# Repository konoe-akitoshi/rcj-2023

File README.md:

# rcj-2023

Program of RoboCup Junior 2023 Soccer Open.

## Member

| Name      | Role                  | Links                                                                                |
| :-------- | :-------------------- | :----------------------------------------------------------------------------------- |
| Akitoshi  | Team Leader, Hardware | [Twitter](https://twitter.com/konoe_akitoshi), [Homepage](https://akitoshi-lab.dev/) |
| ryota2357 | Software (main)       | [Twitter](https://twitter.com/95s7k84695a), [Homepage](https://ryota2357.com/)       |
| sepa38    | Software (vision)     | [Twitter](https://twitter.com/sepa381), [AtCoder](https://atcoder.jp/users/sepa_38)  |
| gae       | Schedule, Chores      | [Twitter](https://twitter.com/gae_uec)                                               |

## Project Layout

```
.
├── Gyro              Gyro senssor (BNO5055) program.
├── LICENSE           MIT License.
├── MainProgram
│   ├── Program       Main (RP2040) program.
│   ├── Test          Test programs for main RP2040.
├── Motor
│   ├── Program       MotorDriver (ATMega328P) program.
│   └── Test          Test programs for MotorDriver.
├── README.md
├── Terminal
│   ├── Program       Main LCD (Wio Terminal) program.
│   └── Tests         Test programs for Main LCD.
└── Vison-M1n
    ├── Calibration   Check and calculate camera calibration paramaters.
    ├── Program       Vison (M1n) protrams.
    └── Tests         Test programs for Vision.
```

## Wiki

Our wiki are available at [Here](https://github.com/konoe-akitoshi/rcj-2023/wiki)

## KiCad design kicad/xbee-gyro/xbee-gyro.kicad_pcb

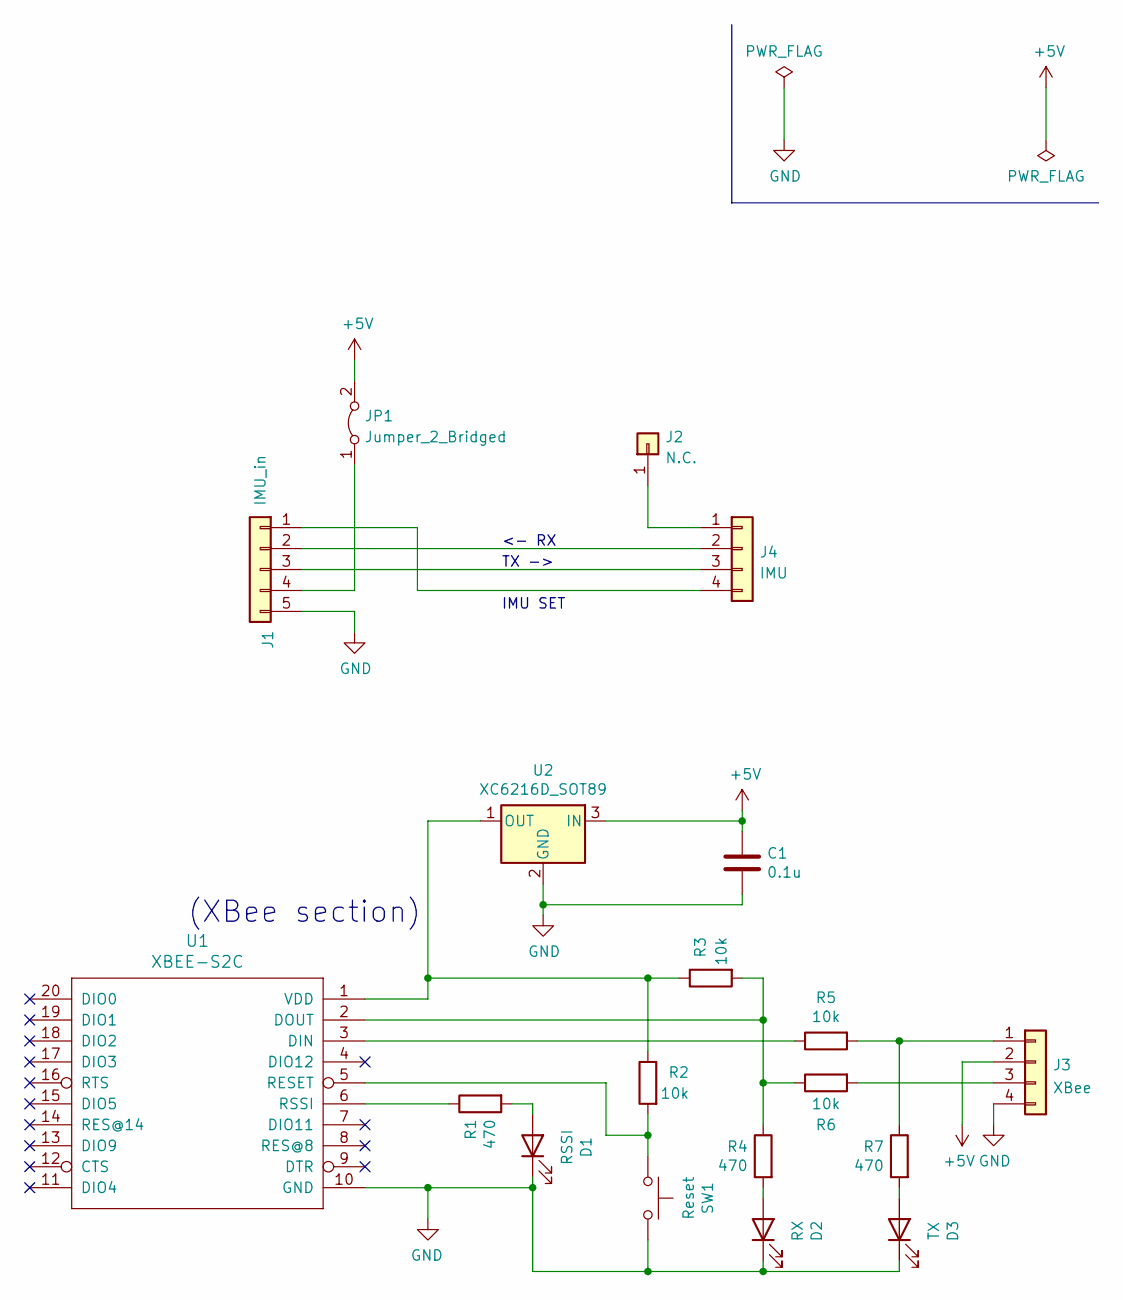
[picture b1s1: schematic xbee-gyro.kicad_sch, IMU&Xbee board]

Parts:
C1: 0.1u; C_0603_1608Metric_Pad1.08x0.95mm_HandSolder
D1: RSSI; LED_0603_1608Metric_Pad1.05x0.95mm_HandSolder
D2: RX; LED_0603_1608Metric_Pad1.05x0.95mm_HandSolder
D3: TX; LED_0603_1608Metric_Pad1.05x0.95mm_HandSolder
J1: IMU_in; PinHeader_1x05_P1.27mm_Vertical
J2: N.C.; PinHeader_1x01_P2.54mm_Vertical
J3: XBee; PinSocket_1x04_P2.54mm_Vertical
J4: IMU; PinSocket_1x04_P2.54mm_Vertical
JP1: Jumper_2_Bridged; SolderJumper-2_P1.3mm_Bridged_Pad1.0x1.5mm
R1, R4, R7: 470; R_0603_1608Metric_Pad0.98x0.95mm_HandSolder
R2, R3, R5, R6: 10k; R_0603_1608Metric_Pad0.98x0.95mm_HandSolder
SW1: Reset; THAU13-AB-R
U1: XBEE-S2C
U2: XC6216D_SOT89; SOT-89-3

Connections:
+5V: C1.1, J3.2, JP1.2 (B), U2.3 (IN)
GND: C1.2, D1.1 (K), D2.1 (K), D3.1 (K), J1.5, J3.4, SW1.2, U1.10 (GND), U2.2 (GND)
unnamed: D1.2 (A), R1.2
unnamed: D2.2 (A), R4.2
unnamed: D3.2 (A), R7.2
unnamed: J1.1, J4.4
unnamed: J1.2, J4.2
unnamed: J1.3, J4.3
unnamed: J1.4, JP1.1 (A)
unnamed: J2.1, J4.1
unnamed: J3.1, R5.2, R7.1
unnamed: J3.3, R6.2
unnamed: R1.1, U1.6 (RSSI)
unnamed: R2.1, R3.1, U1.1 (VDD), U2.1 (OUT)
unnamed: R2.2, SW1.1, U1.5 (RESET)
unnamed: R3.2, R4.1, R6.1, U1.2 (DOUT)
unnamed: R5.1, U1.3 (DIN)

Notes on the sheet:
<- RX
(XBee section)
TX ->
IMU SET

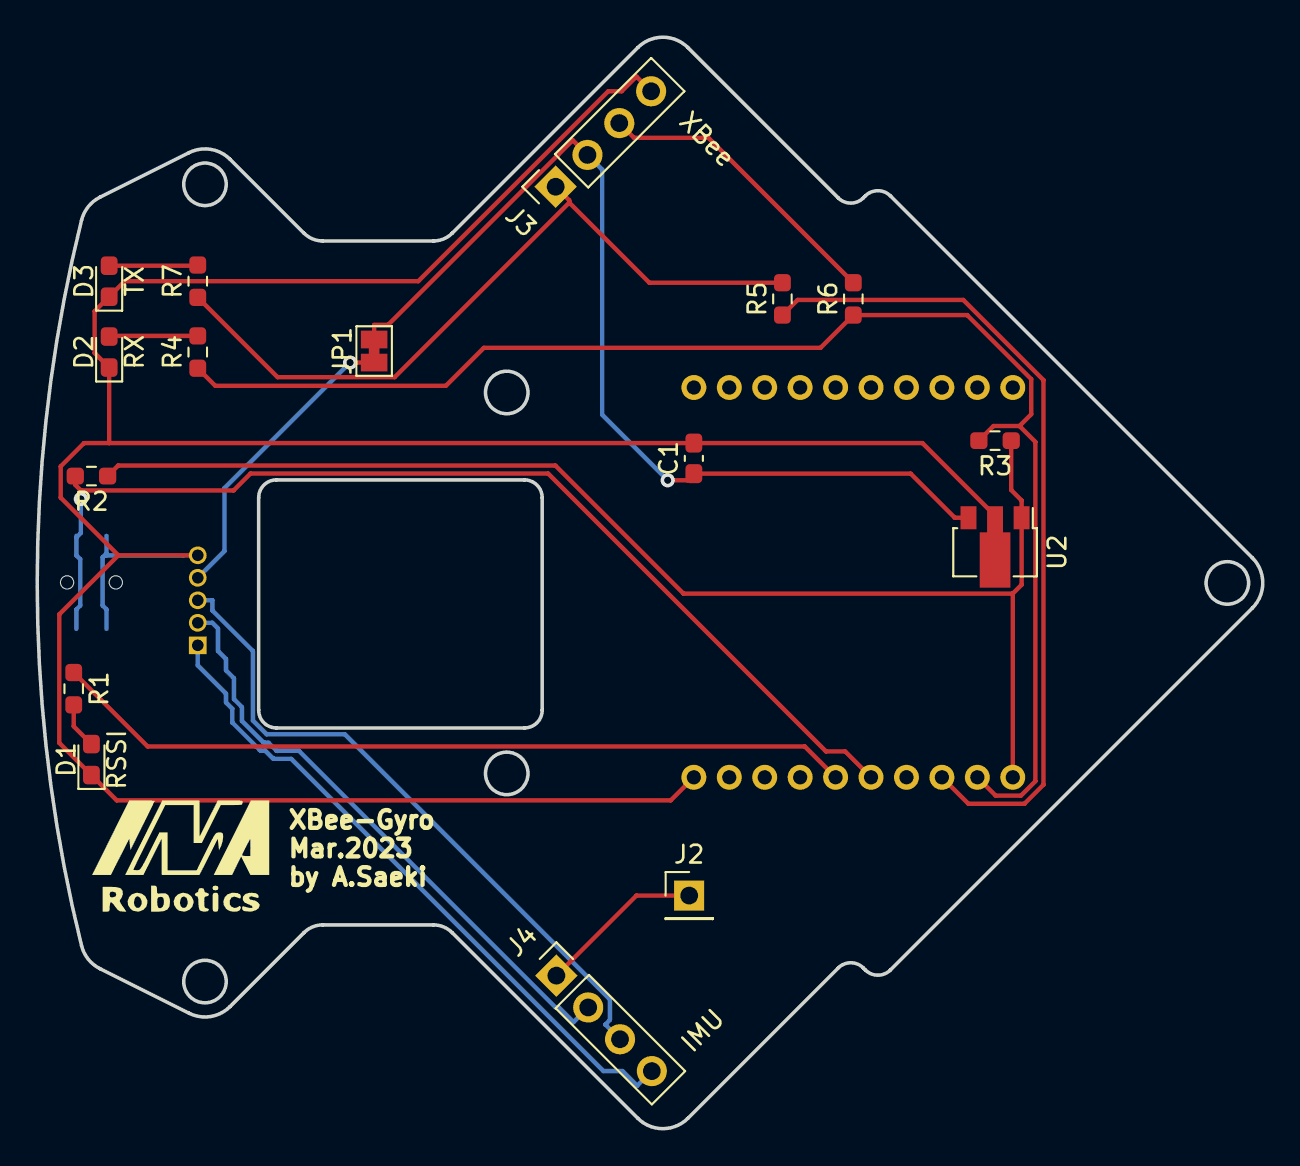
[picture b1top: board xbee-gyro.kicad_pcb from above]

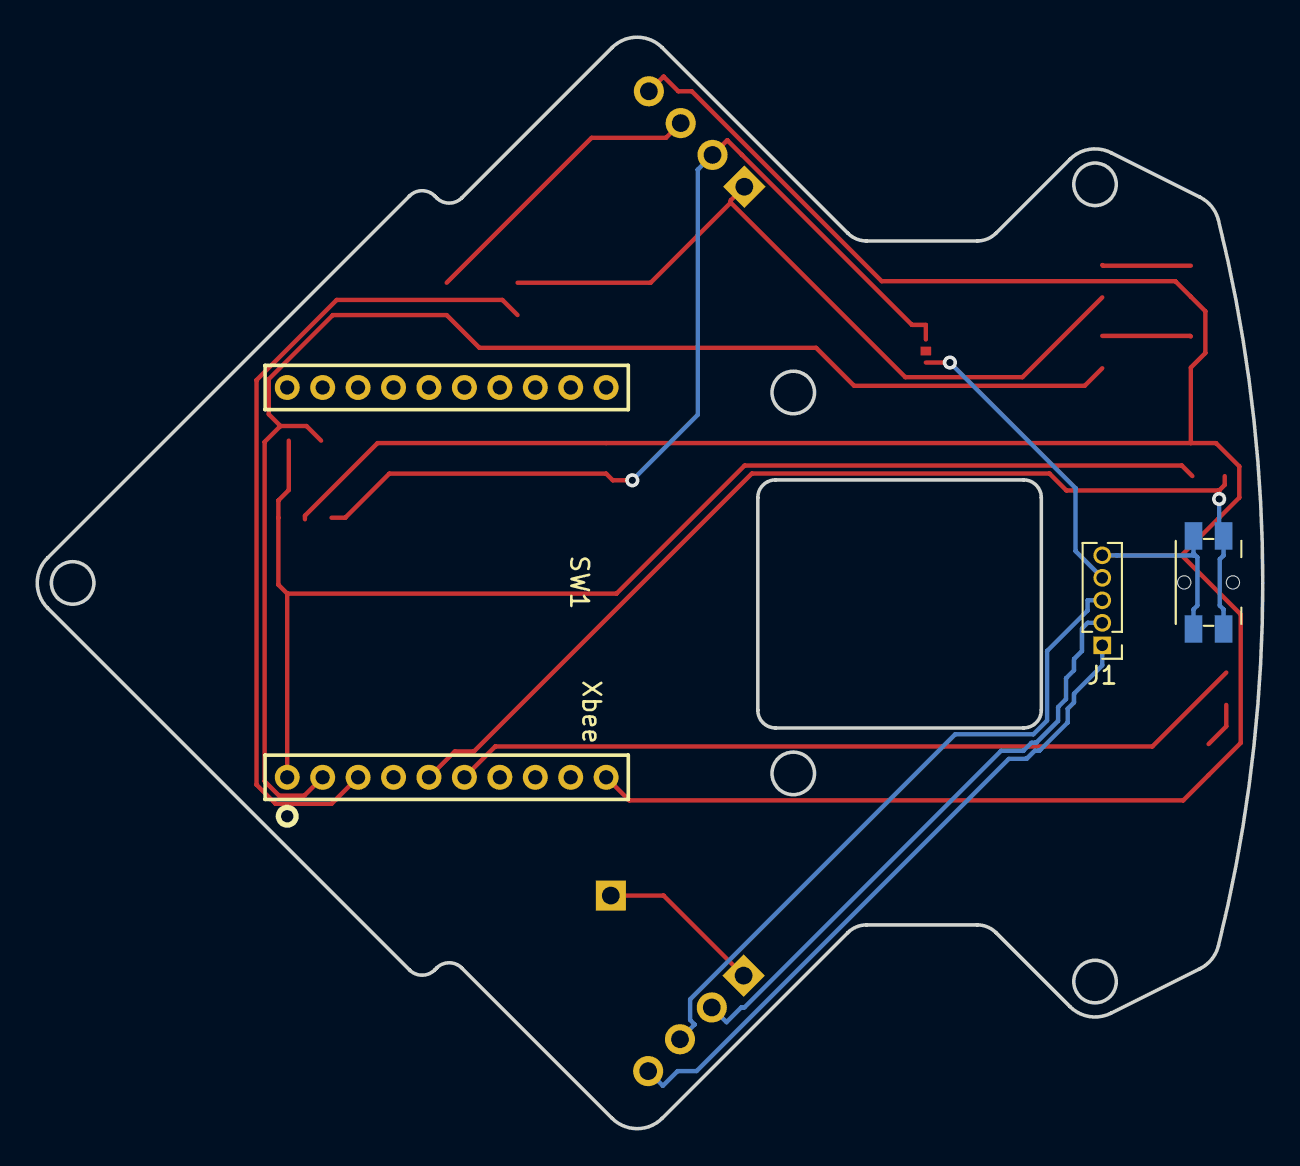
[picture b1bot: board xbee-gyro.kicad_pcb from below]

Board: 2 copper layers, 69.2 x 61.6 mm, 19 parts (3 on the bottom side), 17 nets.

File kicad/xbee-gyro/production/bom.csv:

Designator,Footprint,Quantity,Value,LCSC Part #
C1,0603,1,0.1u,
D1,0603,1,RSSI,
D2,0603,1,RX,
D3,0603,1,TX,
J1,PinHeader_1x05_P1.27mm_Vertical,1,IMU_in,
J2,PinHeader_1x01_P2.54mm_Vertical,1,N.C.,
J3,PinSocket_1x04_P2.54mm_Vertical,1,XBee,
J4,PinSocket_1x04_P2.54mm_Vertical,1,IMU,
JP1,SolderJumper-2_P1.3mm_Bridged_Pad1.0x1.5mm,1,Jumper_2_Bridged,
R1,0603,1,470,
R2,0603,1,10k,
R3,0603,1,10k,
R4,0603,1,470,
R5,0603,1,10k,
R6,0603,1,10k,
R7,0603,1,470,
SW1,THAU13-AB-R,1,Reset,
U1,XBEE-S2C,1,XBEE-S2C,
U2,SOT-89-3,1,XC6216D_SOT89,

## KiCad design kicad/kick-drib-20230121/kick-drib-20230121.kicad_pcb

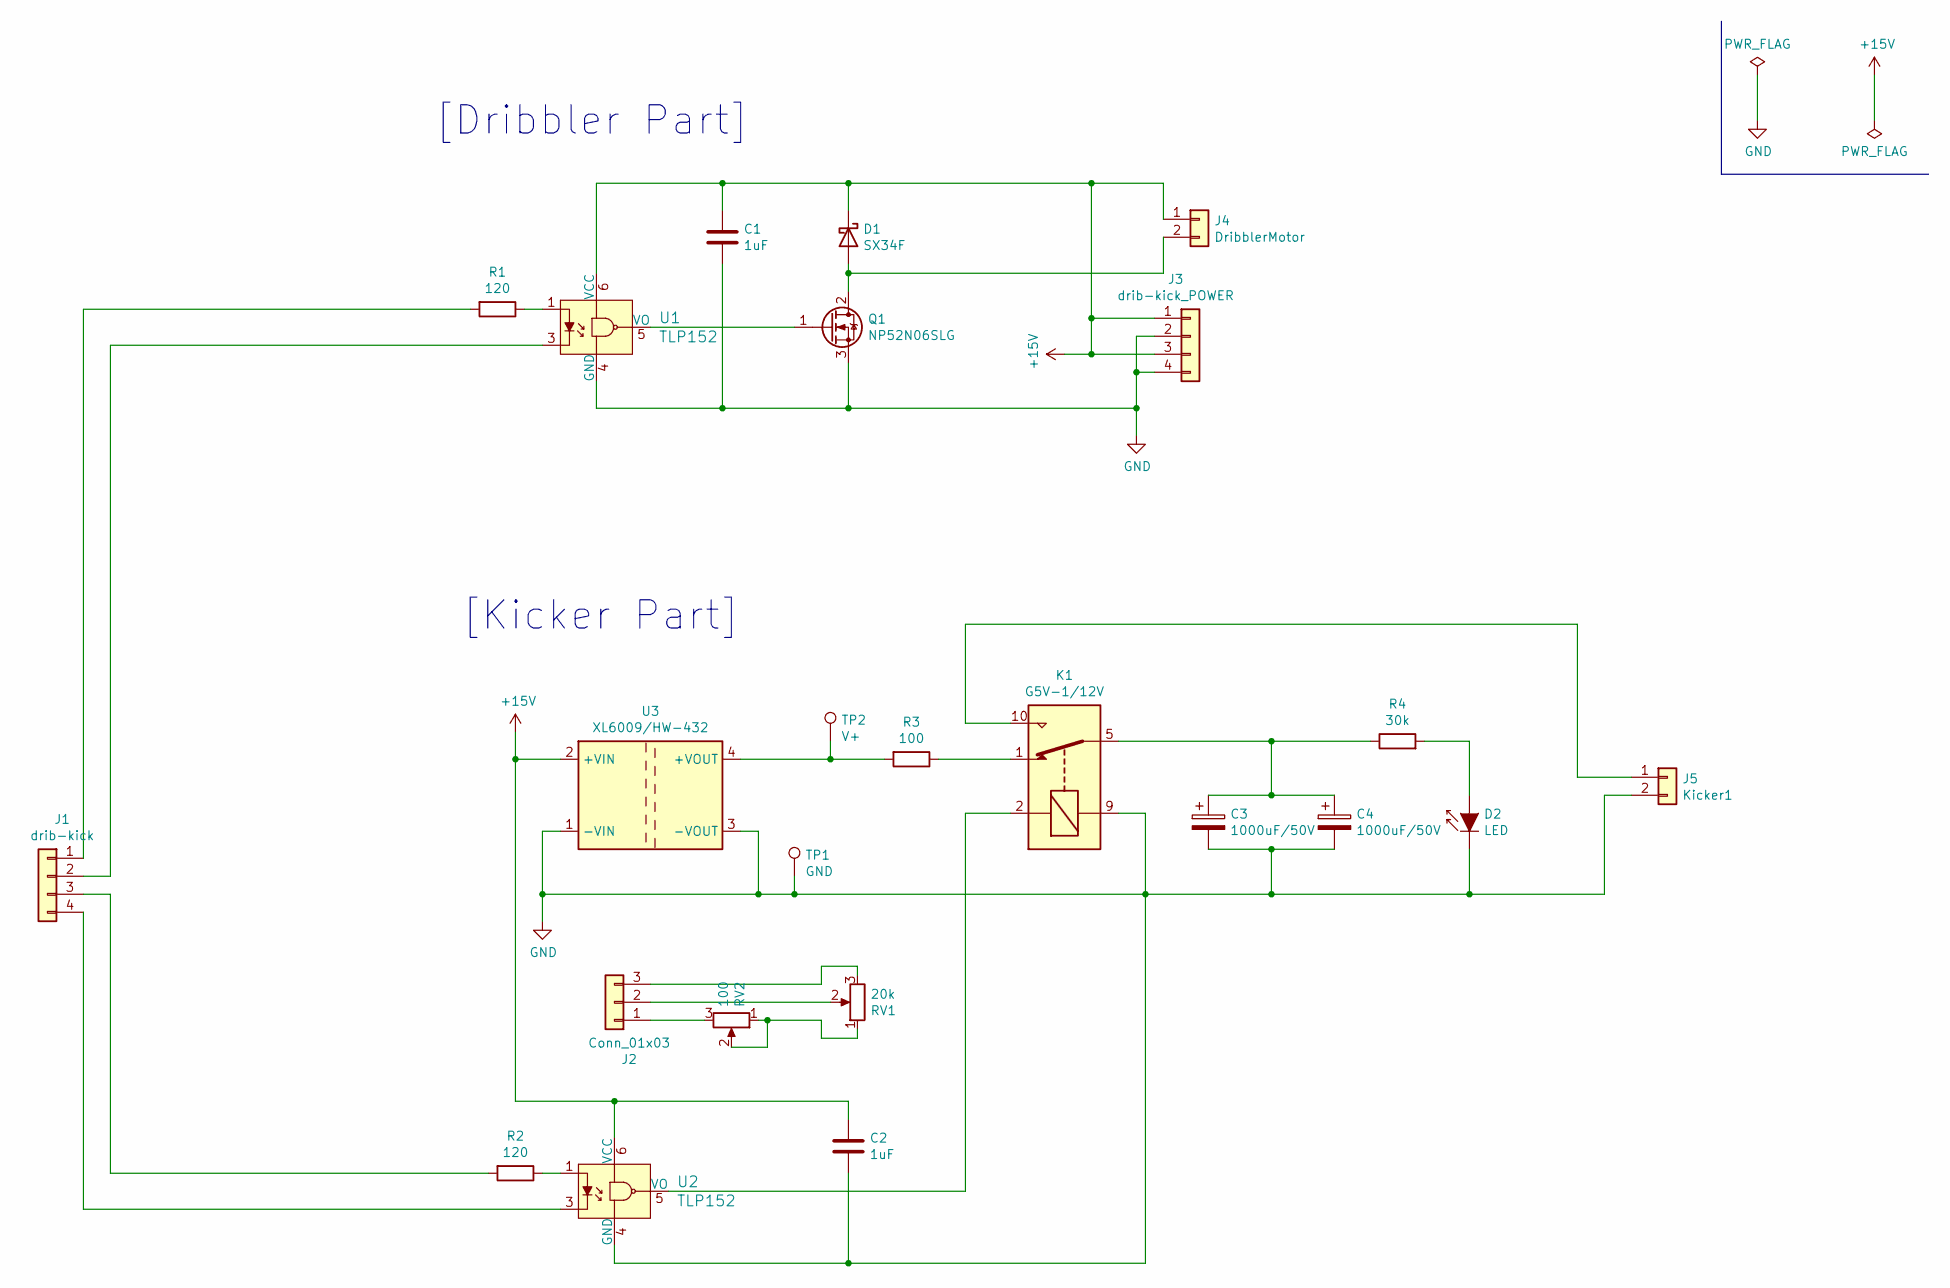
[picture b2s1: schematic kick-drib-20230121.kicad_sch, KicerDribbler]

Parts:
C1, C2: 1uF; C_0603_1608Metric_Pad1.08x0.95mm_HandSolder
C3, C4: 1000uF/50V; CP_Radial_D12.5mm_P7.50mm
D1: SX34F; D_SMA
D2: LED; LED_0603_1608Metric_Pad1.05x0.95mm_HandSolder
J1: drib-kick; PinHeader_1x04_P2.54mm_Vertical
J2: Conn_01x03; PinHeader_1x03_P2.54mm_Vertical
J3: drib-kick_POWER; PinHeader_1x04_P2.54mm_Vertical
J4: DribblerMotor; JST_XH_B2B-XH-A_1x02_P2.50mm_Vertical
J5: Kicker1; JST_XH_B2B-XH-A_1x02_P2.50mm_Vertical
K1: G5V-1/12V; Relay_SPDT_Omron_G5V-1
Q1: NP52N06SLG; TO-252-2
R1, R2: 120; R_0603_1608Metric_Pad0.98x0.95mm_HandSolder
R3: 100; R_Axial_DIN0411_L9.9mm_D3.6mm_P20.32mm_Horizontal
R4: 30k; R_Axial_DIN0204_L3.6mm_D1.6mm_P5.08mm_Horizontal
RV1: 20k; Trim-GF063X
RV2: 100; Trim-GF063P
TP1: GND; TestPoint_Loop_D2.60mm_Drill0.9mm_Beaded
TP2: V+; TestPoint_Loop_D2.60mm_Drill0.9mm_Beaded
U1, U2: TLP152
U3: XL6009/HW-432; XL6009_HW432

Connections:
+15V: C1.1, C2.1, D1.1 (K), J3.1, J3.3, J4.1, U1.6 (VCC), U2.6 (VCC), U3.2 (+VIN)
GND: C1.2, C2.2, C3.2, C4.2, D2.1 (K), J3.2, J3.4, J5.2, K1.9, Q1.3 (S), TP1.1, U1.4 (GND), U2.4 (GND), U3.1 (-VIN), U3.3 (-VOUT)
unnamed: C3.1, C4.1, K1.5, K1.6, R4.1
unnamed: D1.2 (A), J4.2, Q1.2 (D)
unnamed: D2.2 (A), R4.2
unnamed: J1.1, R1.2
unnamed: J1.2, U1.3
unnamed: J1.3, R2.2
unnamed: J1.4, U2.3
unnamed: J2.1, RV2.3
unnamed: J2.2, RV1.2
unnamed: J2.3, RV1.3
unnamed: J5.1, K1.10
unnamed: K1.1, R3.1
unnamed: K1.2, U2.5 (VO)
unnamed: Q1.1 (G), U1.5 (VO)
unnamed: R1.1, U1.1
unnamed: R2.1, U2.1
unnamed: R3.2, TP2.1, U3.4 (+VOUT)
unnamed: RV1.1, RV2.1, RV2.2

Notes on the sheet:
[Kicker Part]
[Dribbler Part]

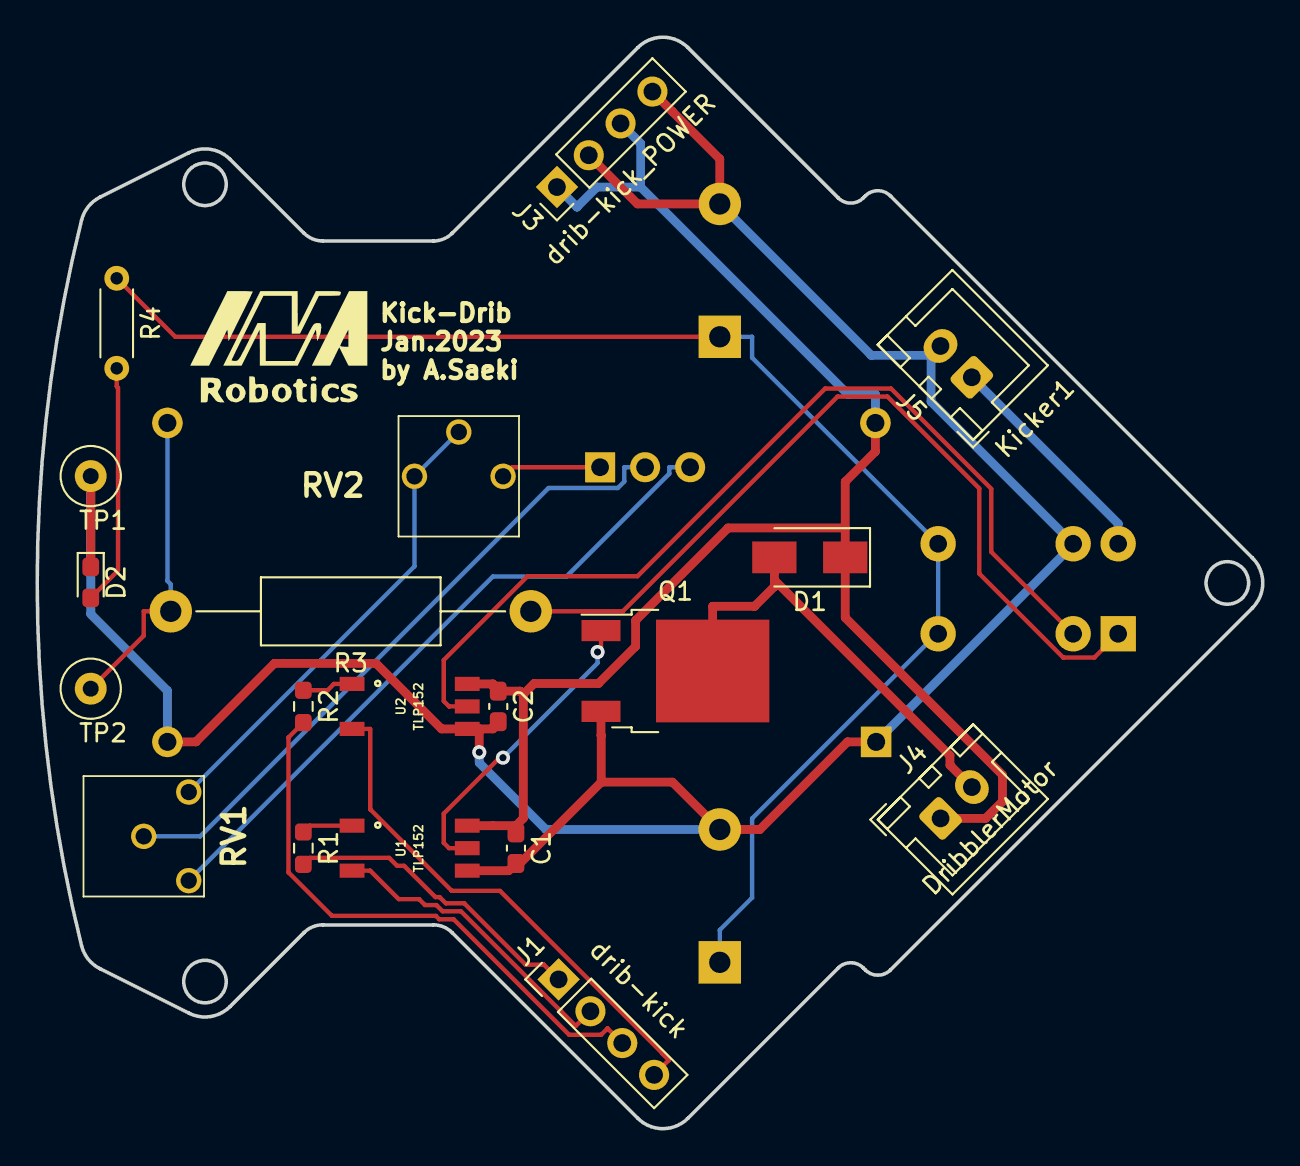
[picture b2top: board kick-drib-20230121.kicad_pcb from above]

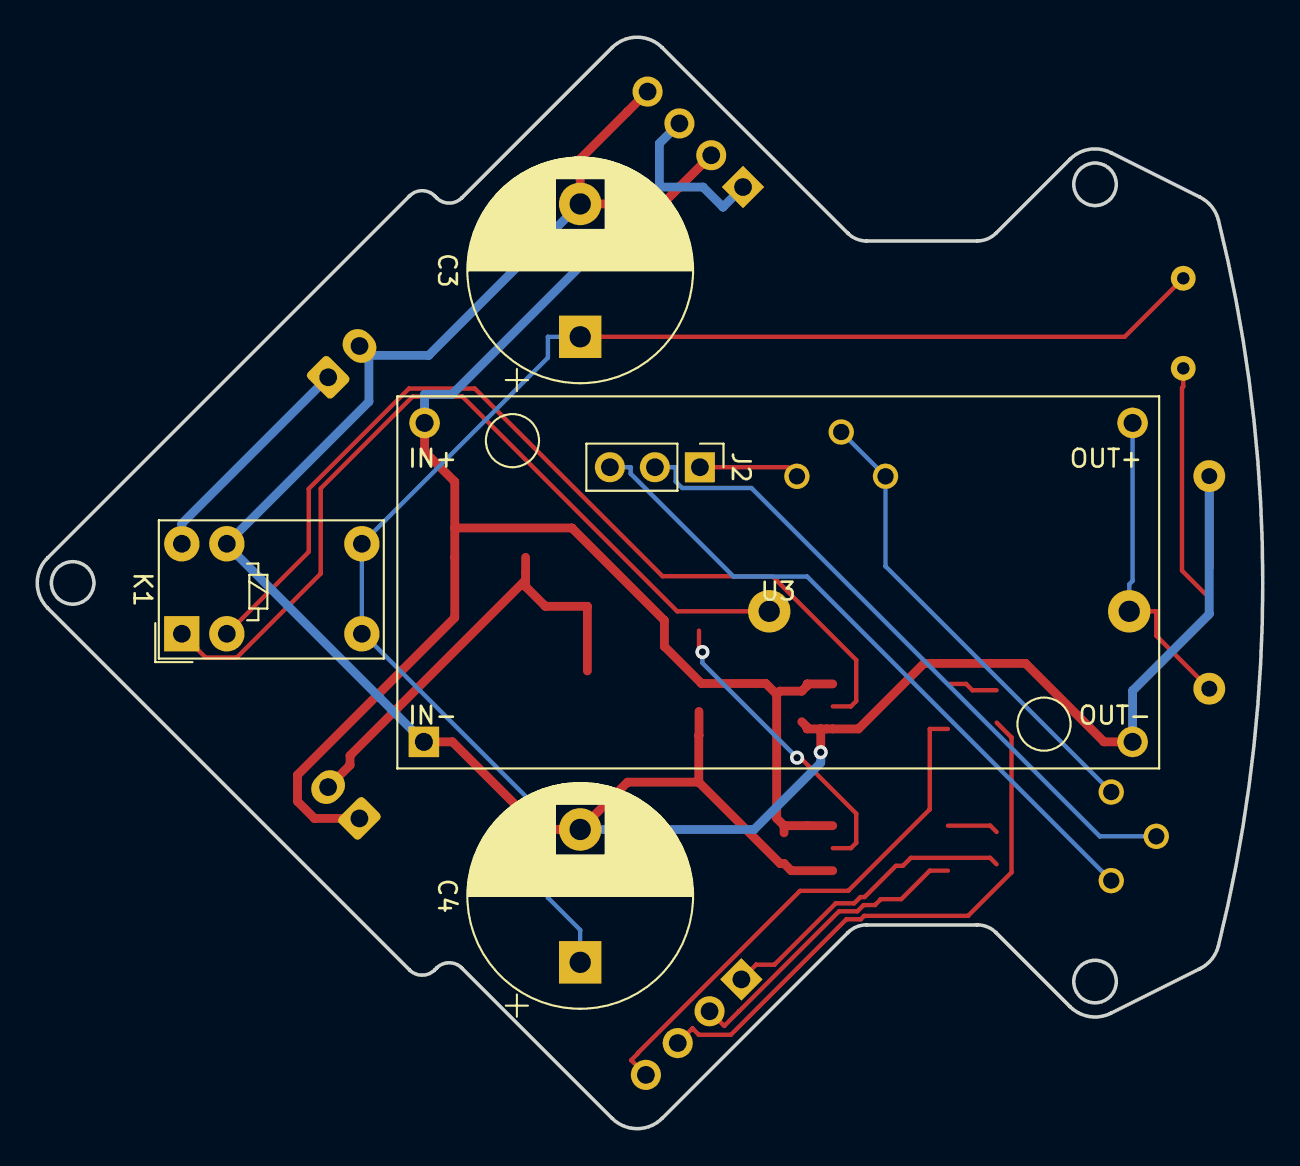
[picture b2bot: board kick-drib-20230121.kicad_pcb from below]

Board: 2 copper layers, 69.2 x 61.6 mm, 24 parts (5 on the bottom side), 20 nets.

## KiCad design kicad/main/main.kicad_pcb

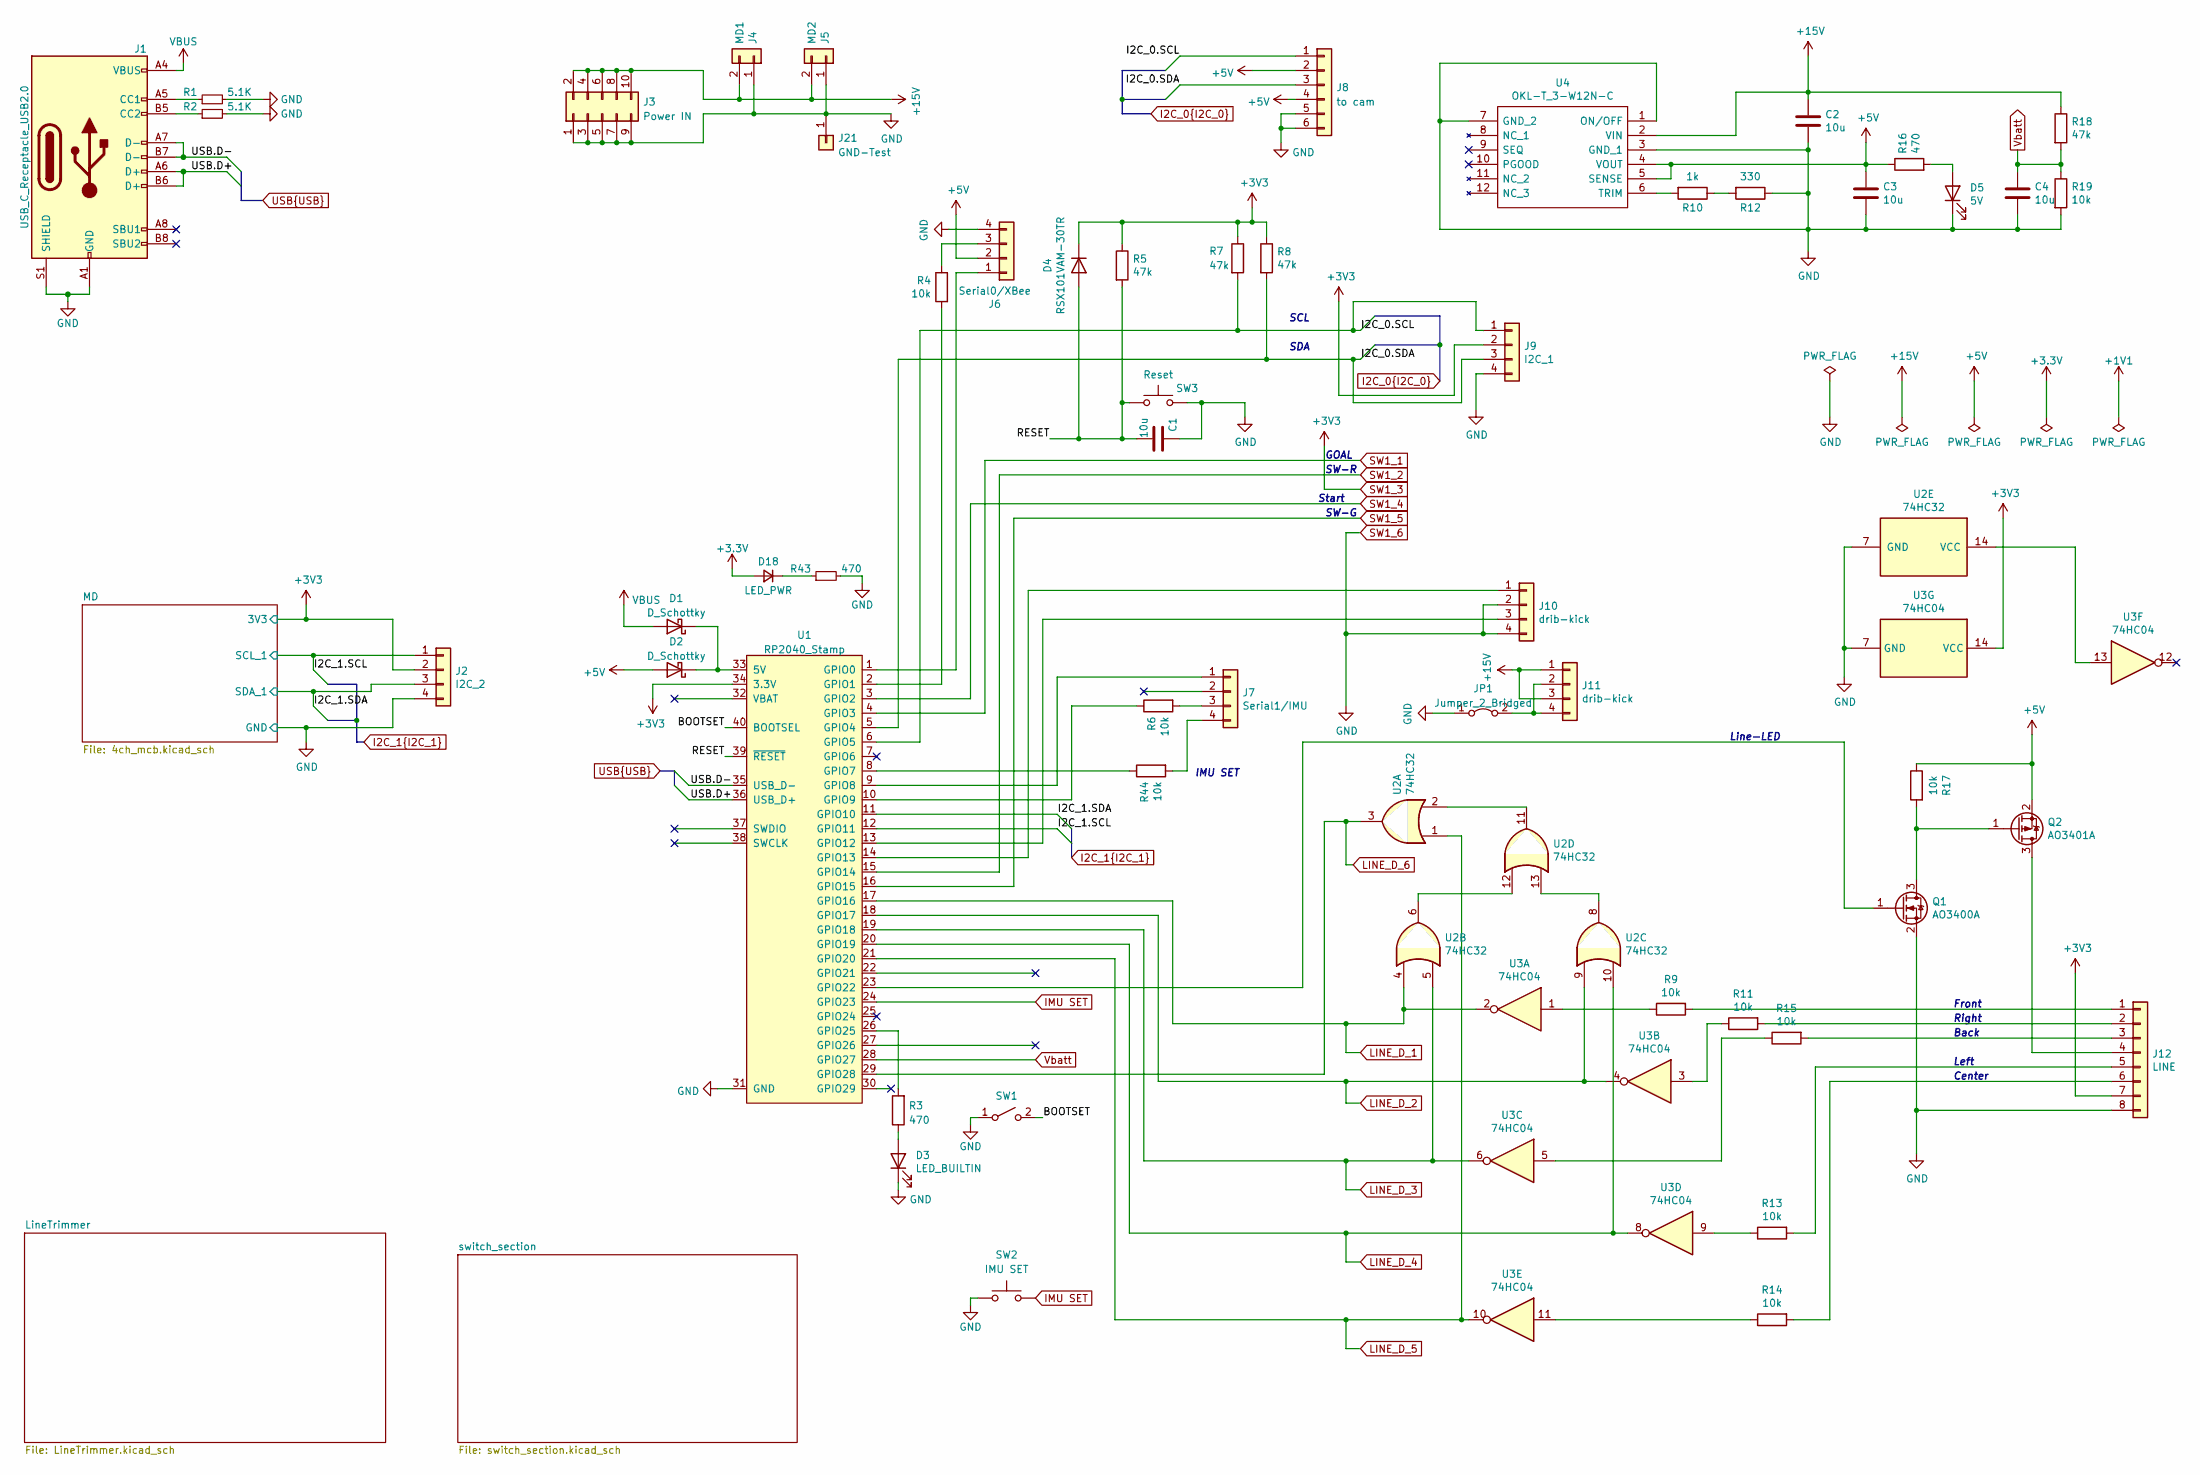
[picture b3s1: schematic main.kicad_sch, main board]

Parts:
C1, C2, C3, C4: 10u; C_0603_1608Metric_Pad1.08x0.95mm_HandSolder
D1, D2: D_Schottky; D_0805_2012Metric_Pad1.15x1.40mm_HandSolder
D3: LED_BUILTIN; LED_SMLE13WBC8W1
D4: RSX101VAM-30TR; D_0805_2012Metric_Pad1.15x1.40mm_HandSolder
D5: 5V; LED_SMLE13WBC8W1
D18: LED_PWR; LED_SMLE13WBC8W1
J1: USB_C_Receptacle_USB2.0; USB_C_Receptacle_XKB_U262-16XN-4BVC11; LCSC C319148
J2: I2C_2; JSTB4B-ZR
J3: Power IN; PinSocket_2x05_P2.54mm_Vertical
J4: MD1; JST_XH_S2B-XH-A-1_1x02_P2.50mm_Horizontal
J5: MD2; JST_XH_S2B-XH-A-1_1x02_P2.50mm_Horizontal
J6: Serial0/XBee; PinHeader_1x04_P2.54mm_Vertical
J7: Serial1/IMU; PinHeader_1x04_P2.54mm_Vertical
J8: to cam; JSTB6B-ZR
J9: I2C_1; JSTB4B-ZR
J10, J11: drib-kick; PinHeader_1x04_P2.54mm_Vertical
J12: LINE; JSTB8B-ZR
J21: GND-Test; PinHeader_1x01_P2.54mm_Vertical
JP1: Jumper_2_Bridged; SolderJumper-2_P1.3mm_Bridged2Bar_RoundedPad1.0x1.5mm
Q1: AO3400A; SOT-23_Handsoldering
Q2: AO3401A; SOT-23_Handsoldering
R1, R2: 5.1K; R_0603_1608Metric
R3, R16, R43: 470; R_0603_1608Metric_Pad0.98x0.95mm_HandSolder
R4, R6, R9, R11, R13, R14, R15, R17, R19, R44: 10k; R_0603_1608Metric_Pad0.98x0.95mm_HandSolder
R5, R7, R8, R18: 47k; R_0603_1608Metric_Pad0.98x0.95mm_HandSolder
R10: 1k; R_Axial_DIN0204_L3.6mm_D1.6mm_P5.08mm_Horizontal
R12: 330; R_Axial_DIN0204_L3.6mm_D1.6mm_P5.08mm_Horizontal
SW1: BOOTSET; THAU13-AB-R; LCSC C318936
SW2: IMU SET; SW_Tactile_Straight_KSA0Axx1LFTR
SW3: Reset; THAU13-AB-R
U1: RP2040_Stamp; RP2040_Stamp_SMD
U2: 74HC32; SOP14W
U3: 74HC04; SOP14W
U4: OKL-T_3-W12N-C; OKL-T3-W12N-C; Manufacturer_Part_Number OKL-T/6-W12N-C; Mouser Part Number 580-OKL-T/6-W12N-C

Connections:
+3.3V: D18.2 (A)
+5V: C3.1, D2.2 (A), J6.2, J8.2, J8.4, Q2.2 (S), R16.1, R17.1, U4.4 (VOUT), U4.5 (SENSE); also elsewhere on the board
+15V: C2.1, J3.2, J3.4, J3.6, J3.8, J3.10, J4.2, J5.2, J11.1, J11.3, R18.1, U4.2 (VIN)
/BOOTSET: SW1.2 (B), U1.40 (BOOTSEL)
/RESET: C1.2, D4.2 (A), R5.2, SW3.1, U1.39 (~RESET)
I2C_0.SCL: J8.1, J9.1, R7.2, U1.6 (GPIO5)
I2C_0.SDA: J8.3, J9.3, R8.2, U1.5 (GPIO4)
I2C_1.SCL: J2.1, U1.12 (GPIO11); also elsewhere on the board
I2C_1.SDA: J2.3, U1.11 (GPIO10); also elsewhere on the board
IMU SET: SW2.2, U1.24 (GPIO23)
LINE_D_1: U1.17 (GPIO16), U2.4, U3.2; also elsewhere on the board
LINE_D_2: U1.18 (GPIO17), U2.9, U3.4; also elsewhere on the board
LINE_D_3: U1.19 (GPIO18), U2.5, U3.6; also elsewhere on the board
LINE_D_4: U1.20 (GPIO19), U2.10, U3.8; also elsewhere on the board
LINE_D_5: U1.21 (GPIO20), U2.1, U3.10; also elsewhere on the board
LINE_D_6: U1.29 (GPIO28), U2.3; also elsewhere on the board
unnamed: D1.1 (K), D2.1 (K), U1.33 (5V)
unnamed: D3.2 (A), R3.1
unnamed: D5.2 (A), R16.2
unnamed: D18.1 (K), R43.1
unnamed: J1.A5 (CC1), R1.1
unnamed: J1.B5 (CC2), R2.1
unnamed: J6.1, U1.1 (GPIO0)
unnamed: J6.3, R4.1
unnamed: J7.1, U1.9 (GPIO8)
unnamed: J7.3, R6.2
unnamed: J7.4, R44.2
unnamed: J10.1, U1.14 (GPIO13)
unnamed: J10.3, U1.13 (GPIO12)
unnamed: J11.2, J11.4, JP1.2 (B)
unnamed: J12.1, R9.2
unnamed: J12.2, R11.2
unnamed: J12.3, R15.2
unnamed: J12.4, Q2.3 (D)
unnamed: J12.5, R13.2
unnamed: J12.6, R14.2
unnamed: Q1.1 (G), U1.23 (GPIO22)
unnamed: Q1.3 (D), Q2.1 (G), R17.2
unnamed: R3.2, U1.26 (GPIO25)
unnamed: R4.2, U1.2 (GPIO1)
unnamed: R6.1, U1.10 (GPIO9)
unnamed: R9.1, U3.1
unnamed: R10.1, R12.2
unnamed: R10.2, U4.6 (TRIM)
unnamed: R11.1, U3.3
unnamed: R13.1, U3.9
unnamed: R14.1, U3.11
unnamed: R15.1, U3.5
unnamed: R44.1, U1.8 (GPIO7)
unnamed: U2.2, U2.11
unnamed: U2.6, U2.12
unnamed: U2.8, U2.13
unnamed: U2.14 (VCC), U3.13
SW1_1: U1.4 (GPIO3); also elsewhere on the board
SW1_2: U1.15 (GPIO14); also elsewhere on the board
SW1_3: D4.1 (K), J2.2, J9.2, J12.7, R5.1, R7.1, R8.1, U1.34 (3.3V), U3.14 (VCC); also elsewhere on the board
SW1_4: U1.3 (GPIO2); also elsewhere on the board
SW1_5: U1.16 (GPIO15); also elsewhere on the board
SW1_6: C1.1, C2.2, C3.2, C4.2, D3.1 (K), D5.1 (K), J1.A1 (GND), J1.A12 (GND), J1.B1 (GND), J1.B12 (GND), J1.S1 (SHIELD), J2.4, J3.1, J3.3, J3.5, J3.7, J3.9, J4.1, J5.1, J6.4, J8.5, J8.6, J9.4, J10.2, J10.4, J12.8, J21.1, JP1.1 (A), Q1.2 (S), R1.2, R2.2, R12.1, R19.2, R43.2, SW1.1 (A), SW2.1, SW3.2, U1.31 (GND), U2.7 (GND), U3.7 (GND), U4.1 (ON/OFF), U4.3 (GND_1), U4.7 (GND_2); also elsewhere on the board
USB.D+: J1.A6 (D+), J1.B6 (D+), U1.36 (USB_D+)
USB.D-: J1.A7 (D-), J1.B7 (D-), U1.35 (USB_D-)
VBUS: D1.2 (A), J1.A4 (VBUS), J1.A9 (VBUS), J1.B4 (VBUS), J1.B9 (VBUS)
Vbatt: C4.1, R18.2, R19.1, U1.28 (GPIO27)

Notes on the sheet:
GOAL
Line-LED
Front
SCL
Back
Left
Center
SDA
IMU SET
Start
Right
SW-G
SW-R

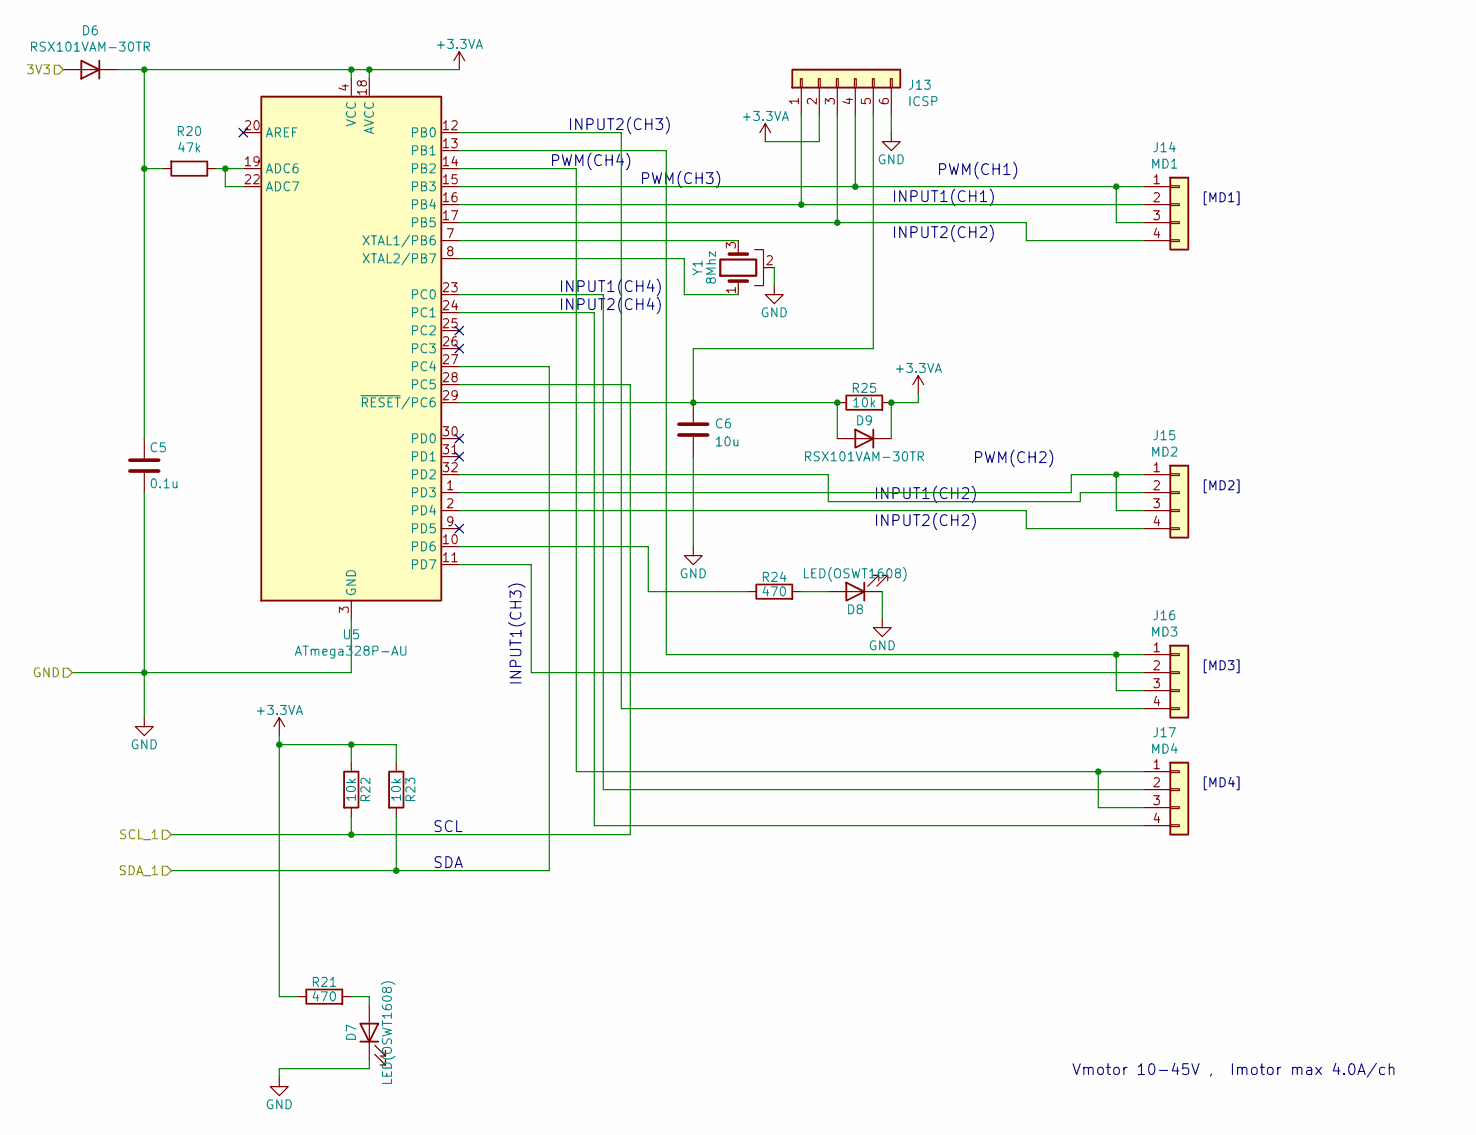
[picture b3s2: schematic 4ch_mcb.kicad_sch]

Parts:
C5: 0.1u; C_0603_1608Metric_Pad1.08x0.95mm_HandSolder
C6: 10u; C_0603_1608Metric_Pad1.08x0.95mm_HandSolder
D6, D9: RSX101VAM-30TR; D_0805_2012Metric_Pad1.15x1.40mm_HandSolder
D7, D8: LED(OSWT1608); LED_0603_1608Metric_Pad1.05x0.95mm_HandSolder
J13: ICSP; JSTB6B-ZR
J14: MD1; JSTS4B-ZRLFSN
J15: MD2; JSTS4B-ZRLFSN
J16: MD3; JSTS4B-ZRLFSN
J17: MD4; JSTS4B-ZRLFSN
R20: 47k; R_0603_1608Metric_Pad0.98x0.95mm_HandSolder
R21, R24: 470; R_0603_1608Metric_Pad0.98x0.95mm_HandSolder
R22, R23, R25: 10k; R_0603_1608Metric_Pad0.98x0.95mm_HandSolder
U5: ATmega328P-AU; TQFP-32_7x7mm_P0.8mm
Y1: 8Mhz; Resonator-3Pin_W6.0mm_H3.0mm

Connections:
+3.3VA: C5.1, D6.1 (K), D9.1 (K), J13.2, R20.2, R21.1, R22.1, R23.1, R25.2, U5.4 (VCC), U5.6 (VCC), U5.18 (AVCC)
I2C_1.SCL: R22.2, U5.28 (PC5); also elsewhere on the board
I2C_1.SDA: R23.2, U5.27 (PC4); also elsewhere on the board
unnamed: C6.1, D9.2 (A), J13.5, R25.1, U5.29 (~RESET/PC6)
unnamed: D7.2 (A), R21.2
unnamed: D8.2 (A), R24.2
unnamed: J13.1, J14.2, U5.16 (PB4)
unnamed: J13.3, J14.4, U5.17 (PB5)
unnamed: J13.4, J14.1, J14.3, U5.15 (PB3)
unnamed: J15.1, J15.3, U5.1 (PD3)
unnamed: J15.2, U5.32 (PD2)
unnamed: J15.4, U5.2 (PD4)
unnamed: J16.1, J16.3, U5.13 (PB1)
unnamed: J16.2, U5.11 (PD7)
unnamed: J16.4, U5.12 (PB0)
unnamed: J17.1, J17.3, U5.14 (PB2)
unnamed: J17.2, U5.23 (PC0)
unnamed: J17.4, U5.24 (PC1)
unnamed: R20.1, U5.19 (ADC6), U5.22 (ADC7)
unnamed: R24.1, U5.10 (PD6)
unnamed: U5.7 (XTAL1/PB6), Y1.3
unnamed: U5.8 (XTAL2/PB7), Y1.1
SW1_3: D6.2 (A); also elsewhere on the board
SW1_6: C5.2, C6.2, D7.1 (K), D8.1 (K), J13.6, U5.3 (GND), U5.5 (GND), U5.21 (GND), Y1.2; also elsewhere on the board

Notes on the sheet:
INPUT2(CH3)
INPUT2(CH2)
PWM(CH1)
PWM(CH3)
PWM(CH2)
INPUT1(CH2)
INPUT1(CH4)
[MD2]
INPUT1(CH3)
[MD4]
INPUT2(CH4)
PWM(CH4)
[MD1]
SDA
[MD3]
Vmotor 10-45V , Imotor max 4.0A/ch
SCL
INPUT1(CH1)

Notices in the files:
parts and their libraries:
Copyright 2021 Accelerated Designs. All rights reserved.
